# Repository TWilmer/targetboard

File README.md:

Targetboard

Warning1: v1 of the board has a bug in the VDD/VSS connection of the CAN drivers. To fix the board lift the power supply pins of the can transceiver chips
Warning2: v1 of the board has a bug in IR receiver footprint pin 1 and 3 are mixed up
Warning3: v1 of the board has the USB connector too near to the Serial Port

What works:
- IR sender
- Leds
- Button
- Serial Port 3
- WIFI port (no SW support yet)
- JTAG, I'm using a recent openocd on RPi B+

this is my hobby project. It supports a lot of features where I want me an my daughter to play with:
- Simulate a Traffic light
- USB to Serial communication
- USB to CAN-Bus (High-Speed only), you need a second board to make some use
- 4 motor drivers
- JTAG probe

The software part is released under GPL2 additionally you have to follow
the original Software's license - e.g. the firmware may be used only
for LPC parts. To compile you need also to install the LPCopen deliver for LPC1769 devices.

The CAD Files are released under GPL2, too. It contains a ZIP
file, which can be used to oder the PCB and if you want also assembly
from SeedStudio - including a proper BOM list.

http://www.seeedstudio.com/service/index.php?r=pcb

So far I have not received any Assembled PCB - so everything is at
your own risk.

This board will use a LPC1768 - as this is availble at SeedStudio, but a LPC1769 should work, too.  A higher clock frequency is possible with LPC1769, but I don't plan to use it.

A set of two assembled board cost around 140$, where you get 3 blank PCBs extra. As SeedStudio is assemblying manually - it should be possible to populate this board also manually.

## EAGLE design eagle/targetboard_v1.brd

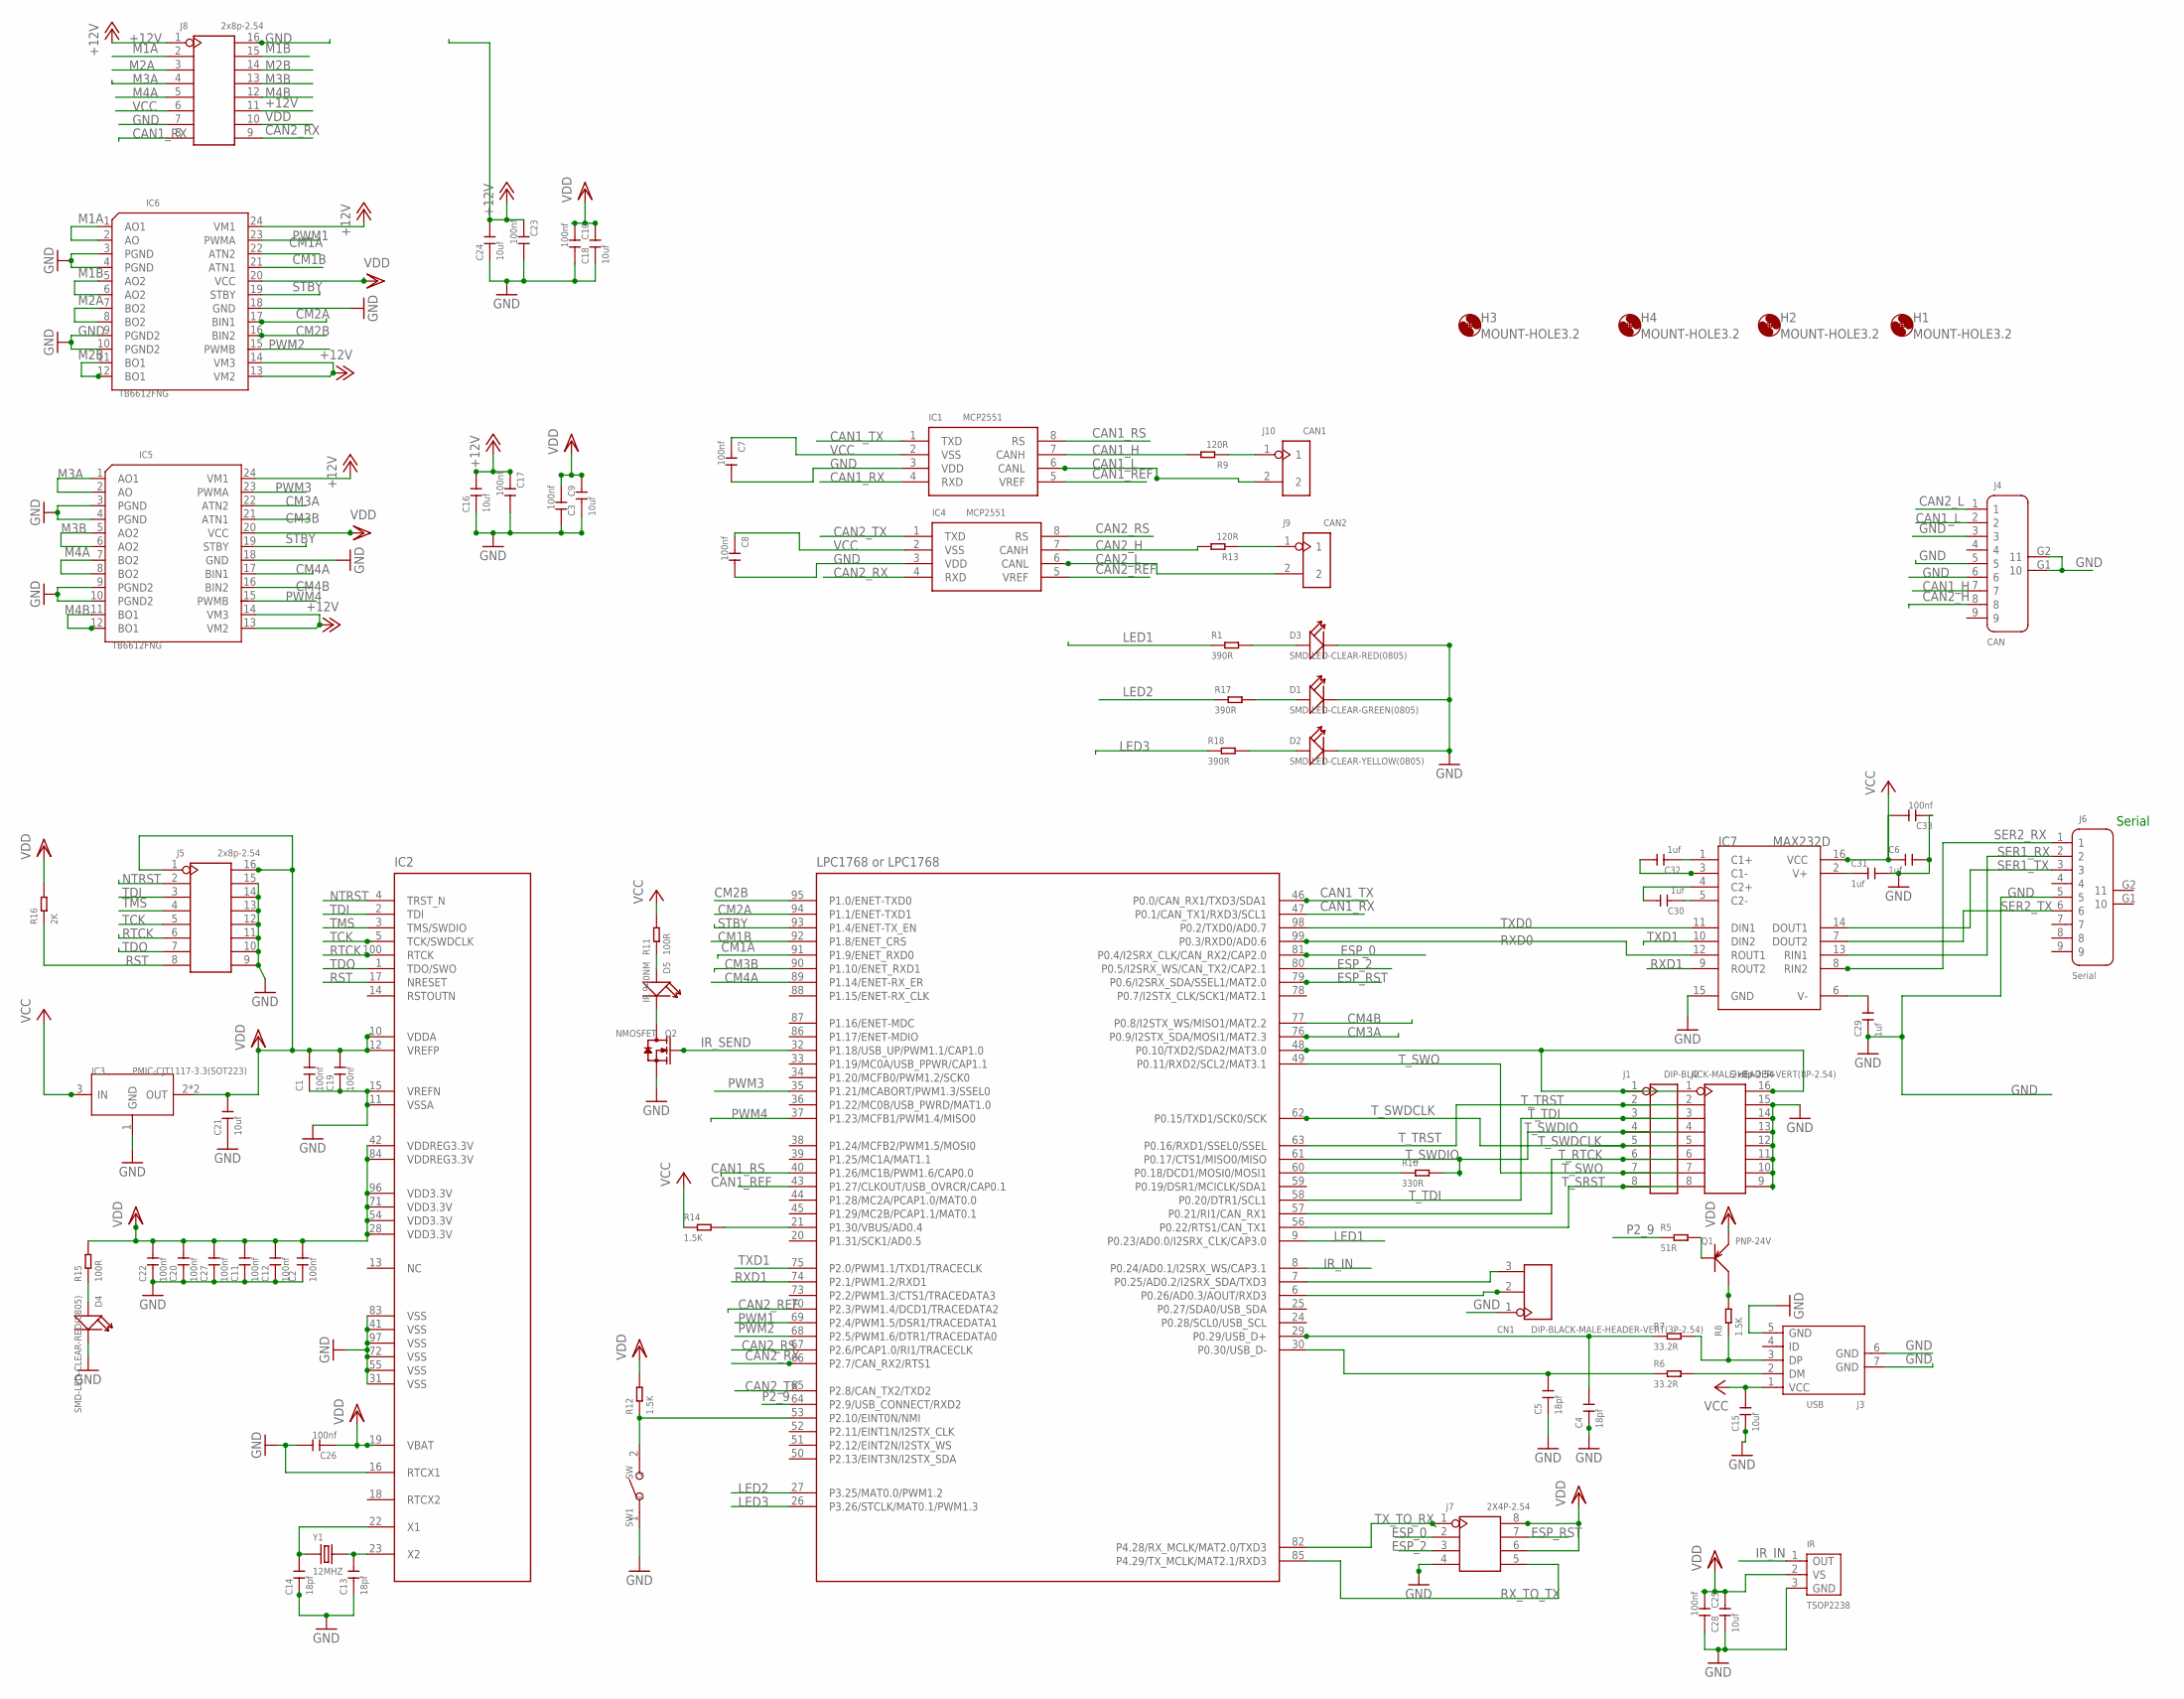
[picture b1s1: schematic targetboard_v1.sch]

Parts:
C1, C2, C7, C8, C9, C10, C11, C12, C17, C19, C20, C22, C23, C25, C26, C27, C33: 100nf; C0805
C3, C16, C18, C21, C24, C28: 10uf; C0805
C4, C5, C13, C14: 18pf; C0805
C6, C29, C30, C31, C32: 1uf; C0805
C15: 10uf; C0603
CN1: DIP-BLACK-MALE-HEADER-VERT(3P-2.54); H3-2.54
D1: SMD-LED-CLEAR-GREEN(0805); LED-0805
D2: SMD-LED-CLEAR-YELLOW(0805); LED-0805
D3, D4: SMD-LED-CLEAR-RED(0805); LED-0805
D5: IR 940NM; LED2-2.54-D5.0MM
H1, H2, H3, H4: MOUNT-HOLE3.2; 3,2
IC1, IC4: MCP2551; SOIC8-1.27-5X4MM
IC2: LPC1768 or LPC1768; LQFP100-0.5-13.8X13.8MM
IC3: PMIC-CJT1117-3.3(SOT223); SOT-223
IC5, IC6: TB6612FNG; SSOP24-0.65-8.9X5.3MM
IC7: MAX232D; SOIC16-1.27-10X3.9MM
IR: TSOP2238; SNR3-2.54-6.95X6.0X5.6MM
J1: DIP-BLACK-MALE-HEADER-VERT(8P-2.54); H8-2.54
J2, J5, J8: 2x8p-2.54; H2X8-2.54
J3: USB; MICRO-USB5+2P-SMD-0.65
J4: CAN; DSUB9+2P-2.77-90D-MALE
J6: Serial; DSUB9+2P-2.77-90D-MALE
J7: 2X4P-2.54; H2X4-2.54
J9: CAN2; H2-2.54
J10: CAN1; H2-2.54
Q1: PNP-24V; SOT-23
Q2: NMOSFET; SOT-23
R1, R17, R18: 390R; R0805
R5: 51R; R0603
R6, R7: 33.2R; R0603
R8, R12, R14: 1.5K; R0805
R9, R13: 120R; R0805
R10: 330R; R0603
R11, R15: 100R; R0805
R16: 2K; R0805
SW1: SW; SW2-2.6-3.0X2.5X1.2+0.4MM
Y1: 12MHZ; X2-SMD-5.0X3.2X1.3MM

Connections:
+12V: C16.2, C17.1, C23.1, C24.2, IC5.13 (VM2), IC5.14 (VM3), IC5.24 (VM1), IC6.13 (VM2), IC6.14 (VM3), IC6.24 (VM1), J8.1, J8.11
CAN1_H: IC1.7 (CANH), J4.7, R9.2
CAN1_L: IC1.6 (CANL), J4.2, J10.2
CAN1_REF: IC1.5 (VREF), IC2.43 (P1.27/CLKOUT/USB_OVRCR/CAP0.1)
CAN1_RS: IC1.8 (RS), IC2.40 (P1.26/MC1B/PWM1.6/CAP0.0)
CAN1_RX: IC1.4 (RXD), IC2.47 (P0.1/CAN_TX1/RXD3/SCL1), J8.8
CAN1_TX: IC1.1 (TXD), IC2.46 (P0.0/CAN_RX1/TXD3/SDA1)
CAN2_H: IC4.7 (CANH), J4.8, R13.2
CAN2_L: IC4.6 (CANL), J4.1, J9.2
CAN2_REF: IC2.70 (P2.3/PWM1.4/DCD1/TRACEDATA2), IC4.5 (VREF)
CAN2_RS: IC2.67 (P2.6/PCAP1.0/RI1/TRACECLK), IC4.8 (RS)
CAN2_RX: IC2.66 (P2.7/CAN_RX2/RTS1), IC4.4 (RXD), J8.9
CAN2_TX: IC2.65 (P2.8/CAN_TX2/TXD2), IC4.1 (TXD)
CM1A: IC2.91 (P1.9/ENET_RXD0), IC6.22 (ATN2)
CM1B: IC2.92 (P1.8/ENET_CRS), IC6.21 (ATN1)
CM2A: IC2.94 (P1.1/ENET-TXD1), IC6.17 (BIN1)
CM2B: IC2.95 (P1.0/ENET-TXD0), IC6.16 (BIN2)
CM3A: IC2.76 (P0.9/I2STX_SDA/MOSI1/MAT2.3), IC5.22 (ATN2)
CM3B: IC2.90 (P1.10/ENET_RXD1), IC5.21 (ATN1)
CM4A: IC2.89 (P1.14/ENET-RX_ER), IC5.17 (BIN1)
CM4B: IC2.77 (P0.8/I2STX_WS/MISO1/MAT2.2), IC5.16 (BIN2)
DM: J3.2 (DM), R6.2
DP: J3.3 (DP), R7.2, R8.1
EDM: C5.2, IC2.30 (P0.30/USB_D-), R6.1
EDP: C4.2, IC2.29 (P0.29/USB_D+), R7.1
ESP_0: IC2.81 (P0.4/I2SRX_CLK/CAN_RX2/CAP2.0), J7.2
ESP_2: IC2.80 (P0.5/I2SRX_WS/CAN_TX2/CAP2.1), J7.3
ESP_RST: IC2.79 (P0.6/I2SRX_SDA/SSEL1/MAT2.0), J7.7
GND: C1.1, C2.1, C3.1, C4.1, C5.1, C6.2, C7.2, C8.2, C9.2, C10.2, C11.1, C12.1, C13.1, C14.1, C15.1, C16.1, C17.2, C18.1, C19.1, C20.1, C21.1, C22.1, C23.2, C24.1, C25.2, C26.2, C27.1, C28.1, C29.1, C31.2, C33.1, CN1.1, D1.-, D2.-, D3.-, D4.-, IC1.3 (VDD), IC2.11 (VSSA), IC2.15 (VREFN), IC2.16 (RTCX1), IC2.31 (VSS), IC2.41 (VSS), IC2.55 (VSS), IC2.72 (VSS), IC2.83 (VSS), IC2.97 (VSS), IC3.1 (GND), IC4.3 (VDD), IC5.3 (PGND), IC5.4 (PGND), IC5.9 (PGND2), IC5.10 (PGND2), IC5.18 (GND), IC6.3 (PGND), IC6.4 (PGND), IC6.9 (PGND2), IC6.10 (PGND2), IC6.18 (GND), IC7.15 (GND), IR.3 (GND), J2.9, J2.10, J2.11, J2.12, J2.13, J2.14, J2.15, J3.5 (GND), J3.6 (GND), J3.7 (GND), J4.3, J4.5, J4.6, J4.G1 (10), J4.G2 (11), J5.9, J5.10, J5.11, J5.12, J5.13, J5.14, J5.15, J6.5, J7.4, J8.7, J8.16, Q2.2 (S), SW1.1
IR_IN: IC2.8 (P0.24/AD0.1/I2SRX_WS/CAP3.1), IR.1 (OUT)
IR_SEND: IC2.32 (P1.18/USB_UP/PWM1.1/CAP1.0), Q2.1 (G)
LED1: IC2.9 (P0.23/AD0.0/I2SRX_CLK/CAP3.0), R1.1
LED2: IC2.27 (P3.25/MAT0.0/PWM1.2), R17.1
LED3: IC2.26 (P3.26/STCLK/MAT0.1/PWM1.3), R18.1
M1A: IC6.1 (AO1), IC6.2 (AO), J8.2
M1B: IC6.5 (AO2), IC6.6 (AO2), J8.15
M2A: IC6.7 (BO2), IC6.8 (BO2), J8.3
M2B: IC6.11 (BO1), IC6.12 (BO1), J8.14
M3A: IC5.1 (AO1), IC5.2 (AO), J8.4
M3B: IC5.5 (AO2), IC5.6 (AO2), J8.13
M4A: IC5.7 (BO2), IC5.8 (BO2), J8.5
M4B: IC5.11 (BO1), IC5.12 (BO1), J8.12
unnamed: IC2.48 (P0.10/TXD2/SDA2/MAT3.0), J1.1, J2.1, J2.16
unnamed: IC2.53 (P2.10/EINT0N/NMI), R12.1, SW1.2
unnamed: D2.+, R18.2
unnamed: D1.+, R17.2
unnamed: D3.+, R1.2
unnamed: C14.2, IC2.22 (X1), Y1.1
unnamed: Q1.3 (C), R8.2
unnamed: C13.2, IC2.23 (X2), Y1.2
unnamed: Q1.1 (B), R5.2
unnamed: IC2.21 (P1.30/VBUS/AD0.4), R14.2
unnamed: J10.1, R9.1
unnamed: J9.1, R13.1
unnamed: D5.+, R11.1
unnamed: C30.2, IC7.4 (C2+)
unnamed: C30.1, IC7.5 (C2-)
unnamed: C32.1, IC7.1 (C1+)
unnamed: C32.2, IC7.3 (C1-)
unnamed: C29.2, IC7.6 (V-)
unnamed: C31.1, IC7.2 (V+)
unnamed: D5.-, Q2.3 (D)
unnamed: IC2.60 (P0.18/DCD1/MOSI0/MOSI1), R10.1
unnamed: D4.+, R15.1
NTRST: IC2.4 (TRST_N), J5.2
P2_9: IC2.64 (P2.9/USB_CONNECT/RXD2), R5.1
PWM1: IC2.69 (P2.4/PWM1.5/DSR1/TRACEDATA1), IC6.23 (PWMA)
PWM2: IC2.68 (P2.5/PWM1.6/DTR1/TRACEDATA0), IC6.15 (PWMB)
PWM3: IC2.35 (P1.21/MCABORT/PWM1.3/SSEL0), IC5.23 (PWMA)
PWM4: IC2.37 (P1.23/MCFB1/PWM1.4/MISO0), IC5.15 (PWMB)
RST: IC2.17 (NRESET), J5.8, R16.1
RTCK: IC2.100 (RTCK), J5.6
RX3: CN1.2, IC2.6 (P0.26/AD0.3/AOUT/RXD3)
RXD0: IC2.99 (P0.3/RXD0/AD0.6), IC7.12 (ROUT1)
RXD1: IC2.74 (P2.1/PWM1.2/RXD1), IC7.9 (ROUT2)
RX_TO_TX: IC2.85 (P4.29/TX_MCLK/MAT2.1/RXD3), J7.5
SER1_RX: IC7.13 (RIN1), J6.2
SER1_TX: IC7.14 (DOUT1), J6.3
SER2_RX: IC7.8 (RIN2), J6.1
SER2_TX: IC7.7 (DOUT2), J6.6
STBY: IC2.93 (P1.4/ENET-TX_EN), IC5.19 (STBY), IC6.19 (STBY)
TCK: IC2.5 (TCK/SWDCLK), J5.5
TDI: IC2.2 (TDI), J5.3
TDO: IC2.1 (TDO/SWO), J5.7
TMS: IC2.3 (TMS/SWDIO), J5.4
TX3: CN1.3, IC2.7 (P0.25/AD0.2/I2SRX_SDA/TXD3)
TXD0: IC2.98 (P0.2/TXD0/AD0.7), IC7.11 (DIN1)
TXD1: IC2.75 (P2.0/PWM1.1/TXD1/TRACECLK), IC7.10 (DIN2)
TX_TO_RX: IC2.82 (P4.28/RX_MCLK/MAT2.0/TXD3), J7.1
T_RTCK: IC2.57 (P0.21/RI1/CAN_RX1), J1.6, J2.6
T_SRST: IC2.56 (P0.22/RTS1/CAN_TX1), J1.8, J2.8
T_SWDCLK: IC2.62 (P0.15/TXD1/SCK0/SCK), J1.5, J2.5
T_SWDIO: IC2.61 (P0.17/CTS1/MISO0/MISO), J1.4, J2.4, R10.2
T_SWO: IC2.49 (P0.11/RXD2/SCL2/MAT3.1), J1.7, J2.7
T_TDI: IC2.58 (P0.20/DTR1/SCL1), J1.3, J2.3
T_TRST: IC2.63 (P0.16/RXD1/SSEL0/SSEL), J1.2, J2.2
VCC: C6.1, C7.1, C8.1, C15.2, C33.2, IC1.2 (VSS), IC3.3 (IN), IC4.2 (VSS), IC7.16 (VCC), J3.1 (VCC), J8.6, R11.2, R14.1
VDD: C1.2, C2.2, C3.2, C9.1, C10.1, C11.2, C12.2, C18.2, C19.2, C20.2, C21.2, C22.2, C25.1, C26.1, C27.2, C28.2, IC2.10 (VDDA), IC2.12 (VREFP), IC2.19 (VBAT), IC2.28 (VDD3.3V), IC2.42 (VDDREG3.3V), IC2.54 (VDD3.3V), IC2.71 (VDD3.3V), IC2.84 (VDDREG3.3V), IC2.96 (VDD3.3V), IC3.2 (OUT), IC3.TER (OUT), IC5.20 (VCC), IC6.20 (VCC), IR.2 (VS), J5.1, J5.16, J7.6, J7.8, J8.10, Q1.2 (E), R12.2, R15.2, R16.2

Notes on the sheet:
Serial

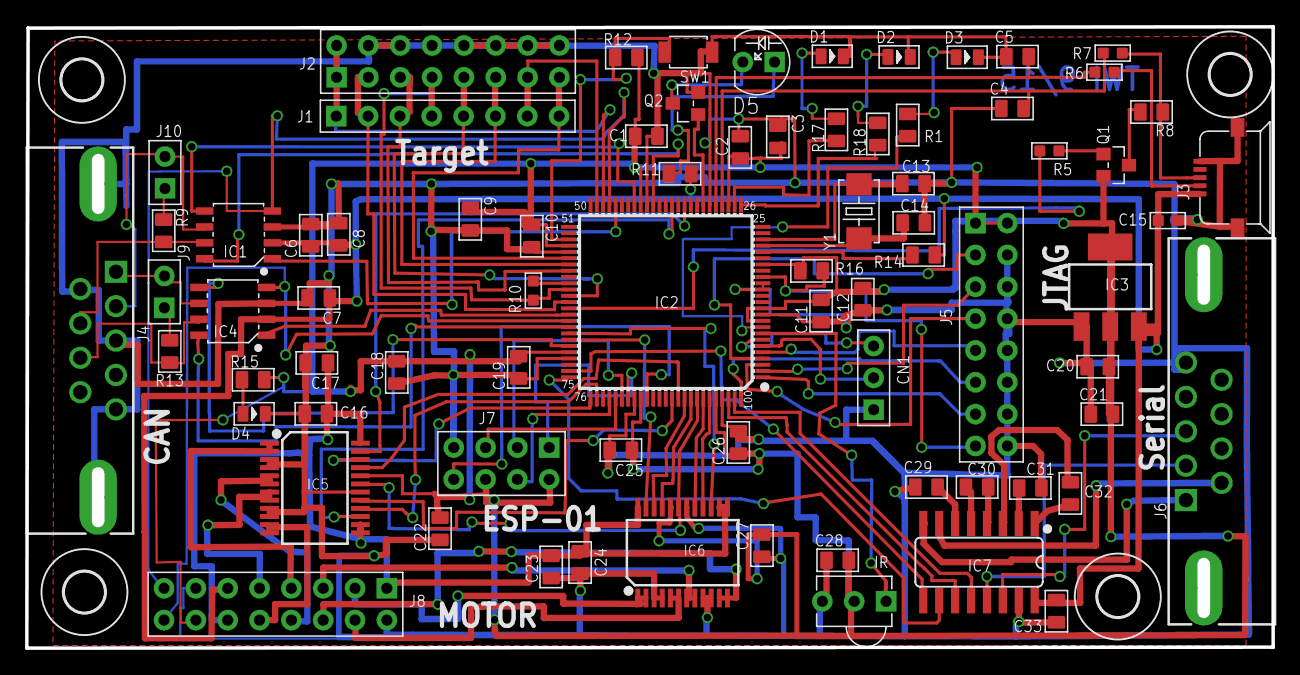
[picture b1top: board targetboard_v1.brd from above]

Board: 2 copper layers, 99.4 x 49.6 mm, 80 parts (0 on the bottom side), 98 nets.

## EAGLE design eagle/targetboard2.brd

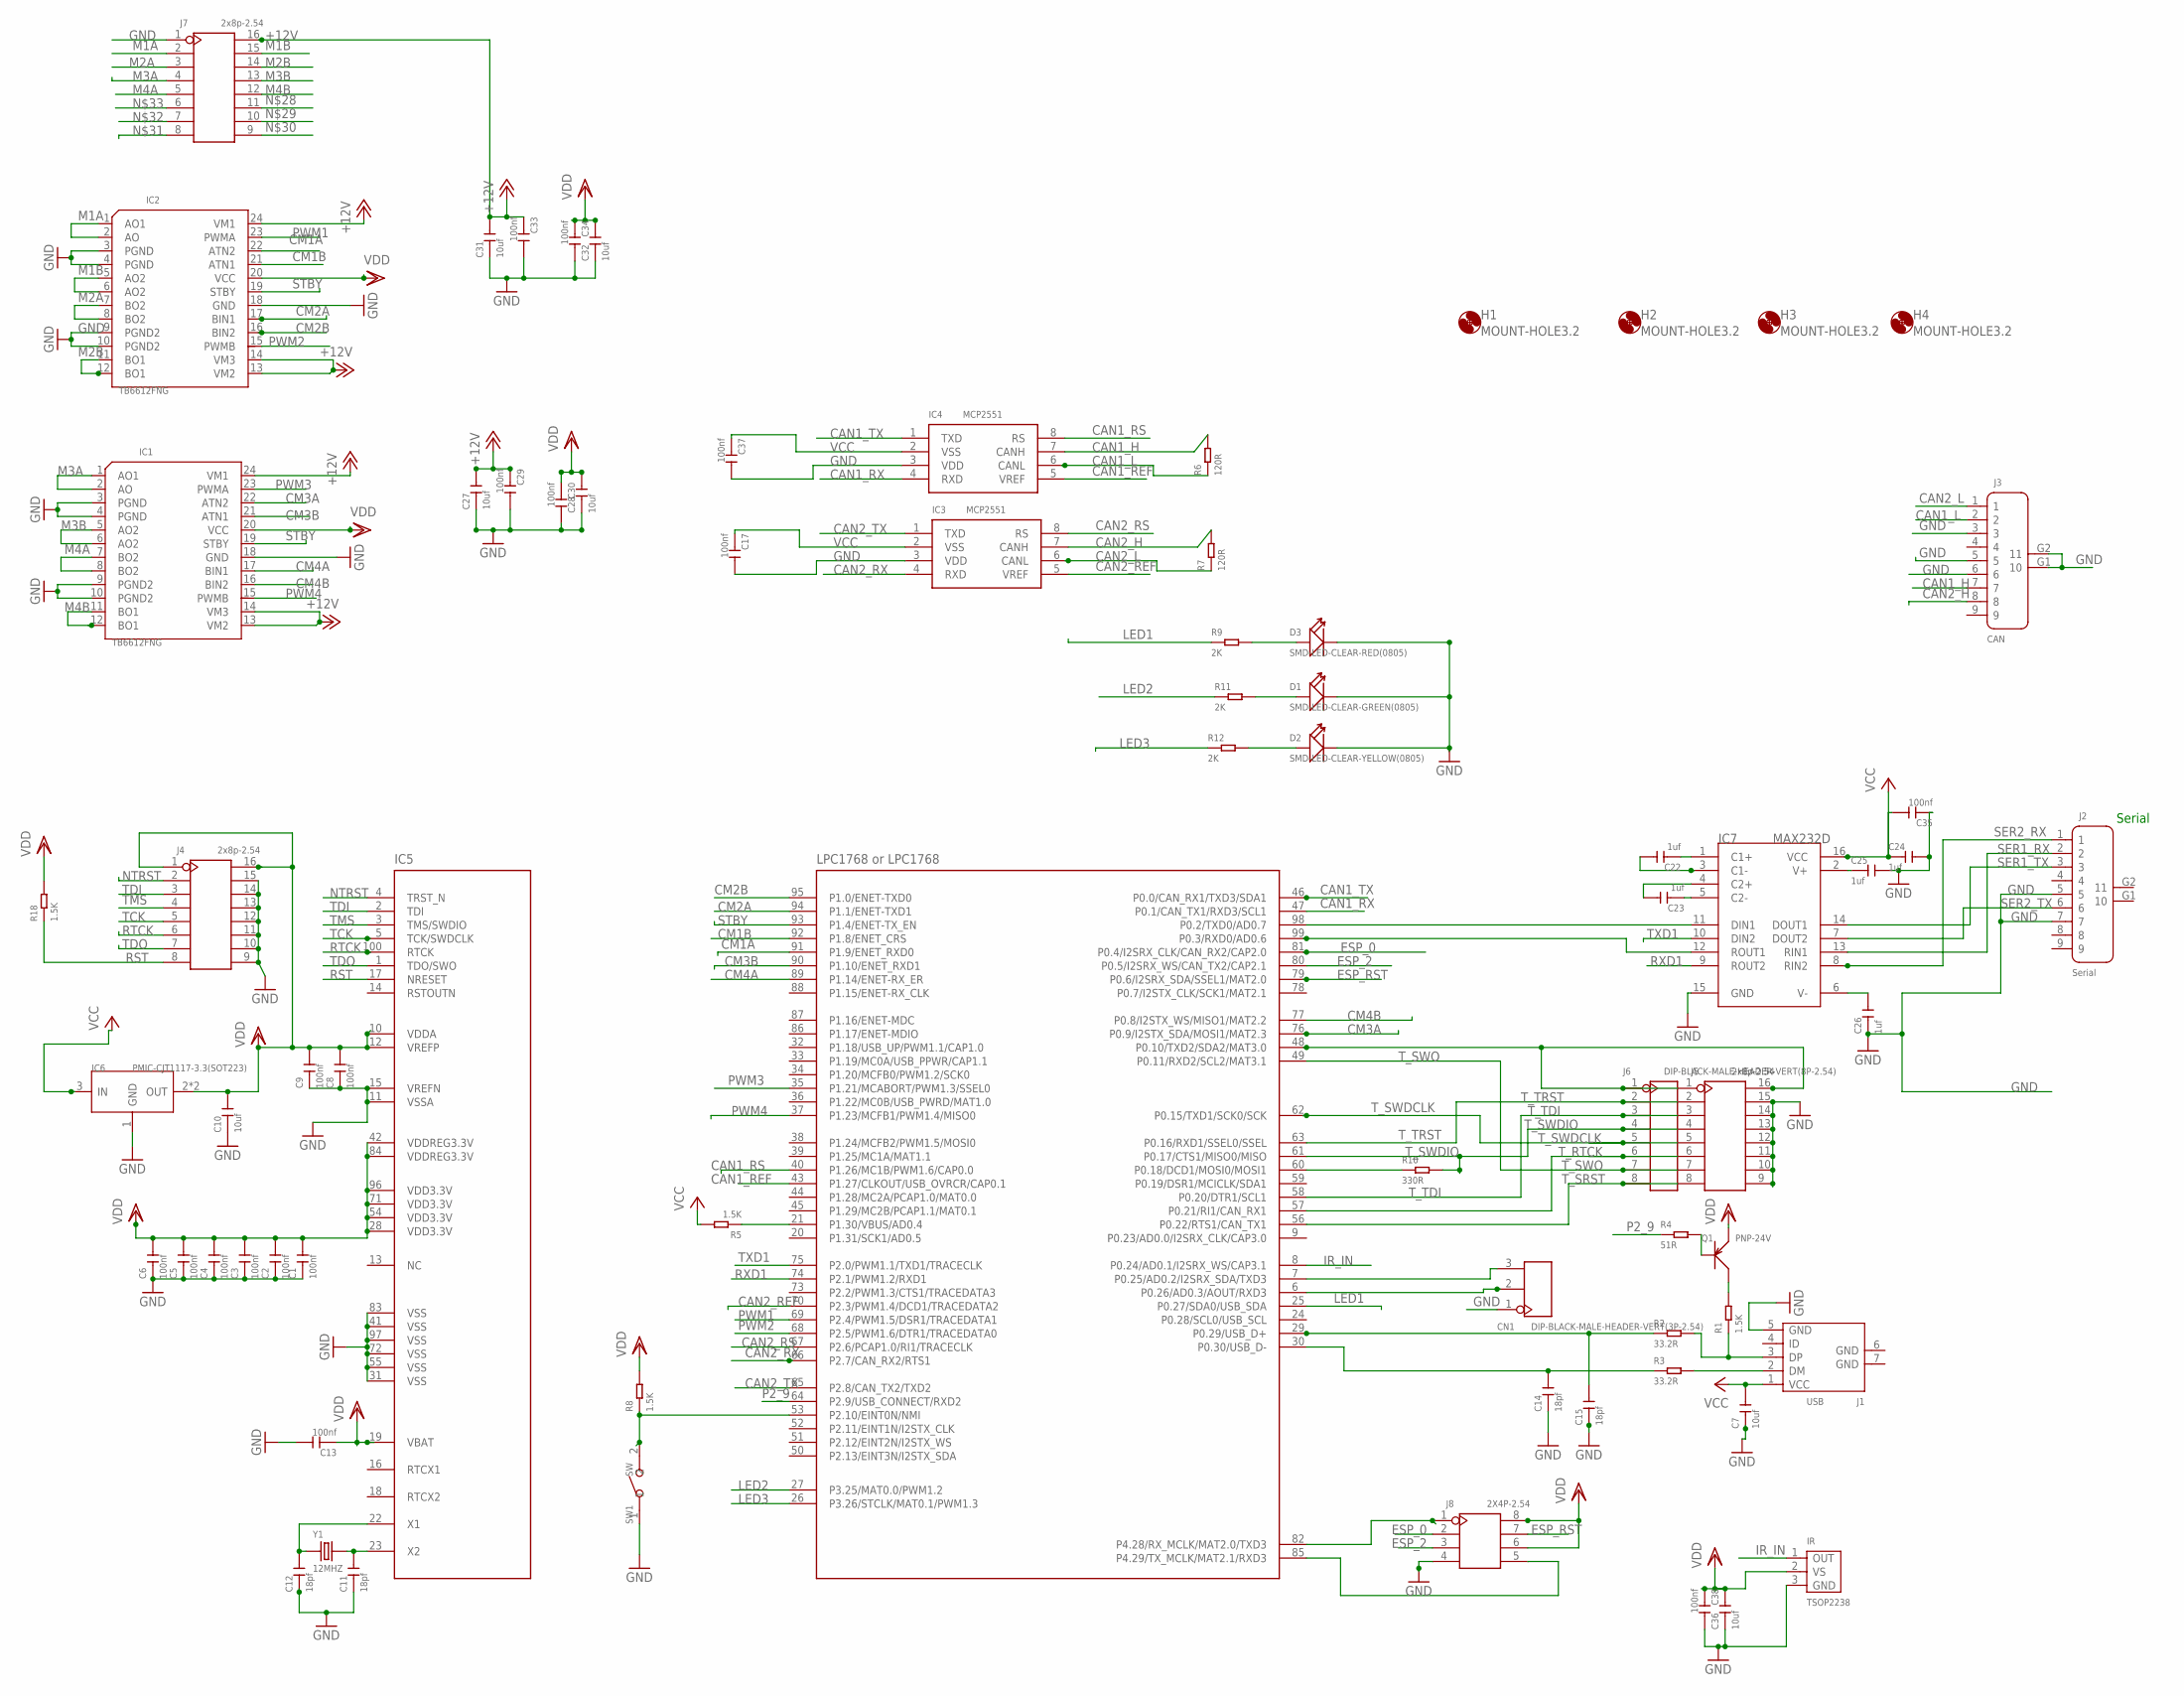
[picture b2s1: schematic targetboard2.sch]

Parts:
C1, C2, C3, C4, C5, C6, C8, C9, C13, C17, C29, C30, C33, C34, C35, C37, C38: 100nf; C0805
C7: 10uf; C0603
C10, C27, C28, C31, C32, C36: 10uf; C0805
C11, C12, C14, C15: 18pf; C0805
C22, C23, C24, C25, C26: 1uf; C0805
CN1: DIP-BLACK-MALE-HEADER-VERT(3P-2.54); H3-2.54
D1: SMD-LED-CLEAR-GREEN(0805); LED-0805
D2: SMD-LED-CLEAR-YELLOW(0805); LED-0805
D3: SMD-LED-CLEAR-RED(0805); LED-0805
H1, H2, H3, H4: MOUNT-HOLE3.2; 3,2
IC1, IC2: TB6612FNG; SSOP24-0.65-8.9X5.3MM
IC3, IC4: MCP2551; SOIC8-1.27-5X4MM
IC5: LPC1768 or LPC1768; LQFP100-0.5-13.8X13.8MM
IC6: PMIC-CJT1117-3.3(SOT223); SOT-223
IC7: MAX232D; SOIC16-1.27-10X3.9MM
IR: TSOP2238; SNR3-2.54-6.95X6.0X5.6MM
J1: USB; MICRO-USB5+2P-SMD-0.65
J2: Serial; DSUB9+2P-2.77-90D-MALE
J3: CAN; DSUB9+2P-2.77-90D-MALE
J4, J5, J7: 2x8p-2.54; H2X8-2.54
J6: DIP-BLACK-MALE-HEADER-VERT(8P-2.54); H8-2.54
J8: 2X4P-2.54; H2X4-2.54
Q1: PNP-24V; SOT-23
R1, R5, R8, R18: 1.5K; R0402
R2, R3: 33.2R; R0603
R4: 51R; R0603
R6, R7: 120R; R0805
R9, R11, R12: 2K; R0805
R10: 330R; R0603
SW1: SW; SW2-2.6-3.0X2.5X1.2+0.4MM
Y1: 12MHZ; X2-SMD-5.0X3.2X1.3MM

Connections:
+12V: C27.2, C29.1, C31.2, C33.1, IC1.13 (VM2), IC1.14 (VM3), IC1.24 (VM1), IC2.13 (VM2), IC2.14 (VM3), IC2.24 (VM1), J7.16
CAN1_H: IC4.7 (CANH), J3.7, R6.2
CAN1_L: IC4.6 (CANL), J3.2, R6.1
CAN1_REF: IC4.5 (VREF), IC5.43 (P1.27/CLKOUT/USB_OVRCR/CAP0.1)
CAN1_RS: IC4.8 (RS), IC5.40 (P1.26/MC1B/PWM1.6/CAP0.0)
CAN1_RX: IC4.4 (RXD), IC5.47 (P0.1/CAN_TX1/RXD3/SCL1)
CAN1_TX: IC4.1 (TXD), IC5.46 (P0.0/CAN_RX1/TXD3/SDA1)
CAN2_H: IC3.7 (CANH), J3.8, R7.2
CAN2_L: IC3.6 (CANL), J3.1, R7.1
CAN2_REF: IC3.5 (VREF), IC5.70 (P2.3/PWM1.4/DCD1/TRACEDATA2)
CAN2_RS: IC3.8 (RS), IC5.67 (P2.6/PCAP1.0/RI1/TRACECLK)
CAN2_RX: IC3.4 (RXD), IC5.66 (P2.7/CAN_RX2/RTS1)
CAN2_TX: IC3.1 (TXD), IC5.65 (P2.8/CAN_TX2/TXD2)
CM1A: IC2.22 (ATN2), IC5.91 (P1.9/ENET_RXD0)
CM1B: IC2.21 (ATN1), IC5.92 (P1.8/ENET_CRS)
CM2A: IC2.17 (BIN1), IC5.94 (P1.1/ENET-TXD1)
CM2B: IC2.16 (BIN2), IC5.95 (P1.0/ENET-TXD0)
CM3A: IC1.22 (ATN2), IC5.76 (P0.9/I2STX_SDA/MOSI1/MAT2.3)
CM3B: IC1.21 (ATN1), IC5.90 (P1.10/ENET_RXD1)
CM4A: IC1.17 (BIN1), IC5.89 (P1.14/ENET-RX_ER)
CM4B: IC1.16 (BIN2), IC5.77 (P0.8/I2STX_WS/MISO1/MAT2.2)
DM: J1.2 (DM), R3.2
DP: J1.3 (DP), R1.1, R2.2
EDM: C14.2, IC5.30 (P0.30/USB_D-), R3.1
EDP: C15.2, IC5.29 (P0.29/USB_D+), R2.1
ESP_0: IC5.81 (P0.4/I2SRX_CLK/CAN_RX2/CAP2.0), J8.2
ESP_2: IC5.80 (P0.5/I2SRX_WS/CAN_TX2/CAP2.1), J8.3
ESP_RST: IC5.79 (P0.6/I2SRX_SDA/SSEL1/MAT2.0), J8.7
GND: C1.1, C2.1, C3.1, C4.1, C5.1, C6.1, C7.1, C8.1, C9.1, C10.1, C11.1, C12.1, C13.2, C14.1, C15.1, C17.2, C24.2, C25.2, C26.1, C27.1, C28.1, C29.2, C30.2, C31.1, C32.1, C33.2, C34.2, C35.1, C36.1, C37.2, C38.2, CN1.1, D1.-, D2.-, D3.-, IC1.3 (PGND), IC1.4 (PGND), IC1.9 (PGND2), IC1.10 (PGND2), IC1.18 (GND), IC2.3 (PGND), IC2.4 (PGND), IC2.9 (PGND2), IC2.10 (PGND2), IC2.18 (GND), IC3.3 (VDD), IC4.3 (VDD), IC5.11 (VSSA), IC5.15 (VREFN), IC5.31 (VSS), IC5.41 (VSS), IC5.55 (VSS), IC5.72 (VSS), IC5.83 (VSS), IC5.97 (VSS), IC6.1 (GND), IC7.15 (GND), IR.3 (GND), J1.5 (GND), J2.5, J2.7, J3.3, J3.5, J3.6, J3.G1 (10), J3.G2 (11), J4.9, J4.10, J4.11, J4.12, J4.13, J4.14, J4.15, J5.9, J5.10, J5.11, J5.12, J5.13, J5.14, J5.15, J7.1, J8.4, SW1.1
IR_IN: IC5.8 (P0.24/AD0.1/I2SRX_WS/CAP3.1), IR.1 (OUT)
LED1: IC5.25 (P0.27/SDA0/USB_SDA), R9.1
LED2: IC5.27 (P3.25/MAT0.0/PWM1.2), R11.1
LED3: IC5.26 (P3.26/STCLK/MAT0.1/PWM1.3), R12.1
M1A: IC2.1 (AO1), IC2.2 (AO), J7.2
M1B: IC2.5 (AO2), IC2.6 (AO2), J7.15
M2A: IC2.7 (BO2), IC2.8 (BO2), J7.3
M2B: IC2.11 (BO1), IC2.12 (BO1), J7.14
M3A: IC1.1 (AO1), IC1.2 (AO), J7.4
M3B: IC1.5 (AO2), IC1.6 (AO2), J7.13
M4A: IC1.7 (BO2), IC1.8 (BO2), J7.5
M4B: IC1.11 (BO1), IC1.12 (BO1), J7.12
unnamed: IC5.48 (P0.10/TXD2/SDA2/MAT3.0), J5.1, J5.16, J6.1
unnamed: IC5.53 (P2.10/EINT0N/NMI), R8.1, SW1.2
unnamed: D2.+, R12.2
unnamed: D1.+, R11.2
unnamed: D3.+, R9.2
unnamed: C12.2, IC5.22 (X1), Y1.1
unnamed: Q1.3 (C), R1.2
unnamed: C11.2, IC5.23 (X2), Y1.2
unnamed: Q1.1 (B), R4.2
unnamed: IC5.21 (P1.30/VBUS/AD0.4), R5.1
unnamed: IC5.85 (P4.29/TX_MCLK/MAT2.1/RXD3), J8.5
unnamed: IC5.98 (P0.2/TXD0/AD0.7), IC7.11 (DIN1)
unnamed: IC5.99 (P0.3/RXD0/AD0.6), IC7.12 (ROUT1)
unnamed: C23.2, IC7.4 (C2+)
unnamed: C23.1, IC7.5 (C2-)
unnamed: C22.1, IC7.1 (C1+)
unnamed: C22.2, IC7.3 (C1-)
unnamed: C26.2, IC7.6 (V-)
unnamed: C25.1, IC7.2 (V+)
unnamed: IC5.60 (P0.18/DCD1/MOSI0/MOSI1), R10.1
unnamed: IC5.82 (P4.28/RX_MCLK/MAT2.0/TXD3), J8.1
NTRST: IC5.4 (TRST_N), J4.2
P2_9: IC5.64 (P2.9/USB_CONNECT/RXD2), R4.1
PWM1: IC2.23 (PWMA), IC5.69 (P2.4/PWM1.5/DSR1/TRACEDATA1)
PWM2: IC2.15 (PWMB), IC5.68 (P2.5/PWM1.6/DTR1/TRACEDATA0)
PWM3: IC1.23 (PWMA), IC5.35 (P1.21/MCABORT/PWM1.3/SSEL0)
PWM4: IC1.15 (PWMB), IC5.37 (P1.23/MCFB1/PWM1.4/MISO0)
RST: IC5.17 (NRESET), J4.8, R18.1
RTCK: IC5.100 (RTCK), J4.6
RX3: CN1.2, IC5.6 (P0.26/AD0.3/AOUT/RXD3)
RXD1: IC5.74 (P2.1/PWM1.2/RXD1), IC7.9 (ROUT2)
SER1_RX: IC7.13 (RIN1), J2.2
SER1_TX: IC7.14 (DOUT1), J2.3
SER2_RX: IC7.8 (RIN2), J2.1
SER2_TX: IC7.7 (DOUT2), J2.6
STBY: IC1.19 (STBY), IC2.19 (STBY), IC5.93 (P1.4/ENET-TX_EN)
TCK: IC5.5 (TCK/SWDCLK), J4.5
TDI: IC5.2 (TDI), J4.3
TDO: IC5.1 (TDO/SWO), J4.7
TMS: IC5.3 (TMS/SWDIO), J4.4
TX3: CN1.3, IC5.7 (P0.25/AD0.2/I2SRX_SDA/TXD3)
TXD1: IC5.75 (P2.0/PWM1.1/TXD1/TRACECLK), IC7.10 (DIN2)
T_RTCK: IC5.57 (P0.21/RI1/CAN_RX1), J5.6, J6.6
T_SRST: IC5.56 (P0.22/RTS1/CAN_TX1), J5.8, J6.8
T_SWDCLK: IC5.62 (P0.15/TXD1/SCK0/SCK), J5.5, J6.5
T_SWDIO: IC5.61 (P0.17/CTS1/MISO0/MISO), J5.4, J6.4, R10.2
T_SWO: IC5.49 (P0.11/RXD2/SCL2/MAT3.1), J5.7, J6.7
T_TDI: IC5.58 (P0.20/DTR1/SCL1), J5.3, J6.3
T_TRST: IC5.63 (P0.16/RXD1/SSEL0/SSEL), J5.2, J6.2
VCC: C7.2, C17.1, C24.1, C35.2, C37.1, IC3.2 (VSS), IC4.2 (VSS), IC6.3 (IN), IC7.16 (VCC), J1.1 (VCC), R5.2
VDD: C1.2, C2.2, C3.2, C4.2, C5.2, C6.2, C8.2, C9.2, C10.2, C13.1, C28.2, C30.1, C32.2, C34.1, C36.2, C38.1, IC1.20 (VCC), IC2.20 (VCC), IC5.10 (VDDA), IC5.12 (VREFP), IC5.19 (VBAT), IC5.28 (VDD3.3V), IC5.42 (VDDREG3.3V), IC5.54 (VDD3.3V), IC5.71 (VDD3.3V), IC5.84 (VDDREG3.3V), IC5.96 (VDD3.3V), IC6.2 (OUT), IC6.TER (OUT), IR.2 (VS), J4.1, J4.16, J8.6, J8.8, Q1.2 (E), R8.2, R18.2

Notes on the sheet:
Serial

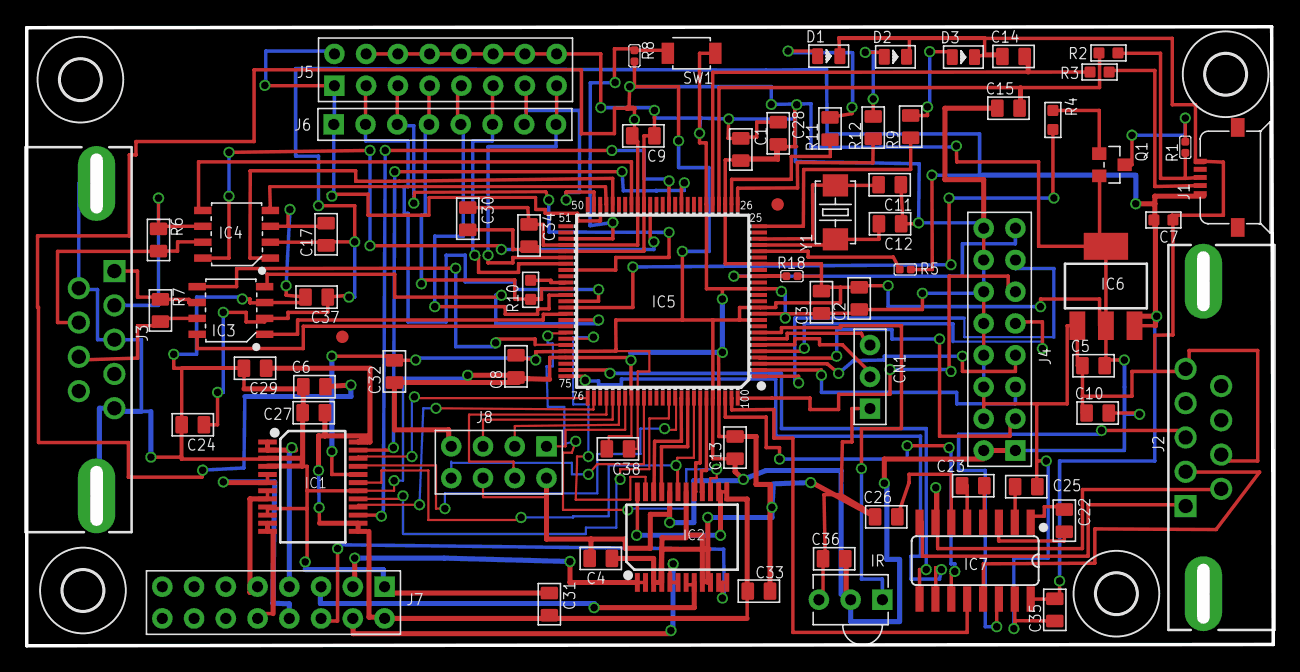
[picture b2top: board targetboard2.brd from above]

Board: 2 copper layers, 99.7 x 49.5 mm, 75 parts (0 on the bottom side), 92 nets.

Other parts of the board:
U$4, U$5: FIDUCIAL_G10

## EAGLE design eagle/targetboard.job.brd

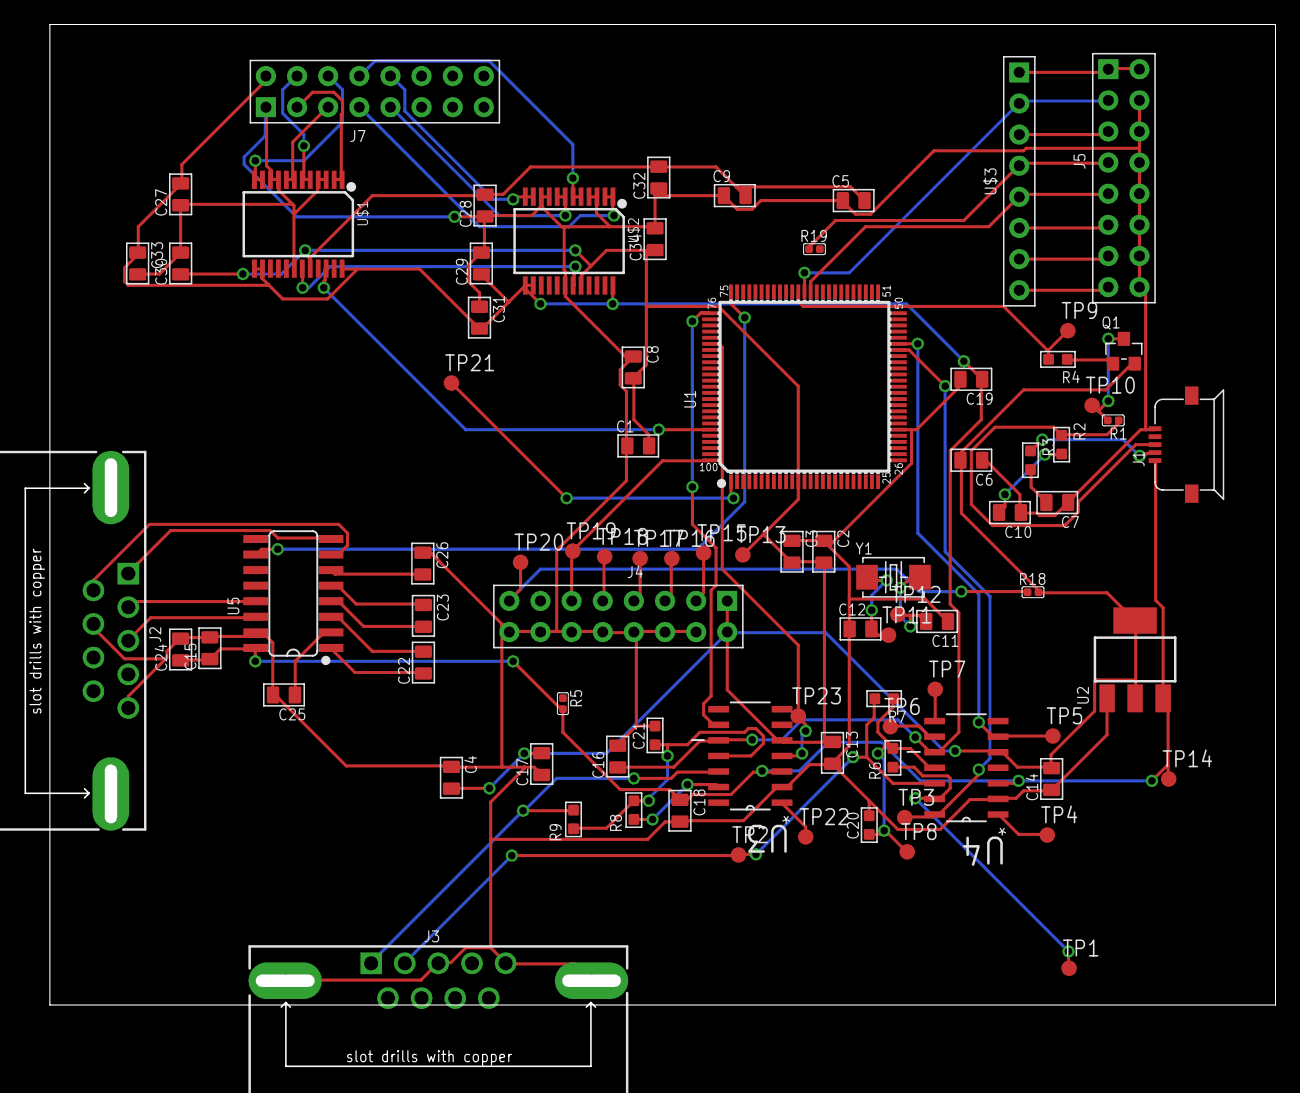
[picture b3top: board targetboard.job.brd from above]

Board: 2 copper layers, 102.0 x 85.0 mm, 84 parts (0 on the bottom side), 77 nets.

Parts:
C1, C2, C3, C4, C5, C6, C8, C9, C13, C14, C15, C16, C17, C18, C19, C29, C30, C33, C34: 100nf; C0805
C7, C10, C11, C12: 18pf; C0805
C20, C21: 22nf; C0603
C22, C23, C24, C25, C26: 1uf; C0805
C27, C28, C31, C32: 10uf; C0805
J1: MICRO-USB5+2P-SMD-0.65
J2, J3: DSUB9+2P-2.77-90D-MALE
J4, J5, J7: 2x8p-2.54; H2X8-2.54
Q1: SOT-23
R1, R5, R18, R19: 1.5K; R0402
R2, R3: 33.2R; R0603
R4: 51R; R0603
R6, R7, R8, R9: 56.2R; R0603
TP1, TP2, TP3, TP4, TP5, TP6, TP7, TP8, TP9, TP10, TP11, TP12, TP13, TP14, TP15, TP16, TP17, TP18, TP19, TP20, TP21, TP22, TP23: TPB1,27; B1,27
U1: LQFP100-0.5-13.8X13.8MM
U2: PMIC-CJT1117-3.3(SOT223); SOT-223
U3, U4: TJA1041AT; SOIC127P600X175-14N
U5: SOIC16-1.27-10X3.9MM
U$1, U$2: SSOP24-0.65-8.9X5.3MM
U$3: DIP-BLACK-MALE-HEADER-VERT(8P-2.54); H8-2.54
Y1: 12MHZ; X2-SMD-5.0X3.2X1.3MM

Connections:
+12V: C16.1, C19.1, C27.2, C29.1, C31.2, C33.1, J7.16, U3.10, U4.10, U$1.13, U$1.14, U$1.24, U$2.13, U$2.14, U$2.24
CAN1_EN: TP5.TP, U1.45, U4.6
CAN1_ERR: TP7.TP, U1.43, U4.8
CAN1_H: J3.7, R6.2, TP1.TP, U4.13
CAN1_L: J3.2, R7.1, TP2.TP, U4.12
CAN1_RX: U1.47, U4.4
CAN1_STB: TP3.TP, U1.44, U4.14
CAN1_TX: TP4.TP, U1.46, U4.1
CAN1_WAKE: TP6.TP, U1.40, U4.9
CAN2_EN: U1.78, U3.6
CAN2_ERR: U1.77, U3.8
CAN2_H: J3.8, R8.2, U3.13
CAN2_L: J3.1, R9.1, U3.12
CAN2_RX: TP23.TP, U1.81, U3.4
CAN2_STB: U1.79, U3.14
CAN2_TX: TP22.TP, U1.80, U3.1
CAN2_WAKE: U1.76, U3.9
CM1A: U1.95, U$1.22
CM3A: U1.91, U$2.22
GND: C1.1, C2.1, C3.1, C4.1, C5.1, C6.1, C7.1, C8.1, C9.1, C10.1, C11.1, C12.1, C13.2, C14.1, C15.2, C16.2, C17.1, C18.2, C19.2, C20.2, C21.2, C24.2, C25.2, C26.1, C27.1, C28.1, C29.2, C30.2, C31.1, C32.1, C33.2, C34.2, J1.5, J2.5, J2.7, J3.3, J3.5, J3.6, J3.G1, J3.G2, J4.9, J4.10, J4.11, J4.12, J4.13, J4.14, J4.15, J5.9, J5.10, J5.11, J5.12, J5.13, J5.14, J5.15, J7.1, U1.11, U1.15, U1.31, U1.41, U1.55, U1.72, U1.83, U1.97, U2.1, U3.2, U4.2, U5.15, U$1.3, U$1.4, U$1.9, U$1.10, U$1.18, U$2.3, U$2.4, U$2.9, U$2.10, U$2.18
M1A: J7.2, U$1.1, U$1.2
M1B: J7.15, U$1.5, U$1.6
M2A: J7.3, U$1.7, U$1.8
M2B: J7.14, U$1.11, U$1.12
M3A: J7.4, U$2.1, U$2.2
M3B: J7.13, U$2.5, U$2.6
M4A: J7.5, U$2.7, U$2.8
M4B: J7.12, U$2.11, U$2.12
unnamed: J5.1, J5.16, U1.48, U$3.1
unnamed: C10.2, R2.1, U1.29
unnamed: C7.2, R3.1, U1.30
unnamed: J1.2, R3.2
unnamed: J1.3, R1.1, R2.2
unnamed: C12.2, TP11.TP, U1.22, Y1.1
unnamed: Q1.3, R1.2, TP10.TP
unnamed: C11.2, TP12.TP, U1.23, Y1.2
unnamed: Q1.1, R4.2
unnamed: R5.1, U1.21
unnamed: C20.1, R6.1, R7.2, TP8.TP, U4.11
unnamed: U1.98, U5.11
unnamed: U1.99, U5.12
unnamed: C21.1, R8.1, R9.2, U3.11
unnamed: C23.2, U5.4
unnamed: C23.1, U5.5
unnamed: C22.1, U5.1
unnamed: C22.2, U5.3
unnamed: C26.2, U5.6
unnamed: C25.1, U5.2
unnamed: R19.2, U1.60
NTRST: J4.2, TP15.TP, U1.4
P2_9: R4.1, TP9.TP, U1.64
PWM1: U1.69, U$1.23
PWM2: U1.68, U$1.15
PWM3: U1.67, U$2.23
PWM4: U1.66, U$2.15
RST: J4.8, R18.1, TP20.TP, U1.17
RTCK: J4.6, TP19.TP, U1.100
RXD1: U1.74, U5.9
SER1_RX: J2.2, U5.13
SER1_TX: J2.3, U5.14
SER2_RX: J2.1, U5.8
SER2_TX: J2.6, U5.7
STBY: U1.87, U$1.19, U$2.19
TCK: J4.5, TP18.TP, U1.5
TDI: J4.3, TP16.TP, U1.2
TDO: TP21.TP, U1.1
TMS: J4.4, TP17.TP, U1.3
TXD1: U1.75, U5.10
T_RTCK: J5.6, U1.57, U$3.6
T_SRST: J5.8, U1.56, U$3.8
T_SWDCLK: J5.5, U1.62, U$3.5
T_SWDIO: J5.4, R19.1, U1.61, U$3.4
T_SWO: J5.7, U1.49, U$3.7
T_TDI: J5.3, U1.58, U$3.3
T_TRST: J5.2, U1.63, U$3.2
VCC: C15.1, C18.1, C24.1, J1.1, R5.2, TP14.TP, U2.3, U3.3, U4.3, U5.16
VDD: C1.2, C2.2, C3.2, C4.2, C5.2, C6.2, C8.2, C9.2, C13.1, C14.2, C17.2, C28.2, C30.1, C32.2, C34.1, J4.1, J4.16, Q1.2, R18.2, TP13.TP, U1.10, U1.12, U1.19, U1.28, U1.42, U1.54, U1.71, U1.84, U1.96, U2.2, U2.TER, U3.5, U4.5, U$1.20, U$2.20

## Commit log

2015-01-26 Working version
2015-01-26 5 COM Interface allocated, one VCOM0 working
2015-01-26 Toggle one LED if something is there on COM3
2015-02-13 COM1 works rest not
2015-02-15 First serial Port passing working on target2
2015-02-15 Working version with loop back and two serial ports.
2015-02-15 Move serial ports to be ACM devices
2015-02-15 Cleanup and add prelimary CAN support
2015-07-25 Add ground for the linux driver
2015-08-09 Add eagle files
2015-08-22 Update of board
2015-08-22 Add README.md
2015-09-20 Fix Board revision, CAN VCC and VSS mixed up
2015-09-20 Board V1 as it was produced
2015-09-20 Add pinout for RPi debugging
2015-09-20 Add openocd configuration to debug with RPI - not RPi2 needs small differences in the configuration
2015-09-21 Adapt license to reflect NXP's stuff, add NXP stuff
2015-09-25 Clean main.c
2015-10-03 add missing files
2015-10-25 Configure pin for UART0
2015-10-25 Add motor control

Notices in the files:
parts and their libraries:
dicons: Copyright (C) 2004, Bob Starr (rtzaudio@mindspring.com)
